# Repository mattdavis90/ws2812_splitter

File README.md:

# WS2812 Splitter

> [!WARNING]
> This project is still very much in beta and I am yet to receive the PCBs and fully verify the desgn.

A configurable splitter compatible with WS2812(B) LEDs. Splits the incoming signal two ways; the first is a copy of the input and the second is disabled for N LED's worth of data. This allows you to run two strips in parallel with each other.

The project is based on the work by [Pete on hackaday.io](https://hackaday.io/project/8181-ws2812b-delay-splitter). As far as I can tell Pete never got it working, this is intended to be a continuation of that work.

The project is being used personally for WS2812B Icicles. Rather than running wires from the bottom of each icicle back to the next LED (to create a continuous strip) this project allows you to place a 'tee' at the top of each icicle, that delays the continuing signal by the length of the drop.

This is maybe best viewed as an image

## Hardware

The design uses a Renesas SLG46826 SPLD to implement the logic required to detect the reset period, count LED words and generate the split signal.

A custom PCB was designed using the TSSOP-20 package to ease soldering. On board are 4 solder jumpers that set the length of the drop; between 0 and 15 LEDs.

### Renesas Greenpak Designer

The Renesas Greenpak software is free to download. I used the Ubuntu version successfully on Fedora. Mac and Windows are also available. This is a screenshot of the design I came up with. I went the multi-programmable chips; a little bit more expensive but I wanted to be sure the design worked and could be tweaked.

*Note*: Counters reset to `N` and trigger on 0 so should be set to `N-1`

Break down of macrocells

* Reset Detector
    - WS2812 datasheet states a minimum 50us reset period - data line held low
    - CNT0 is clocked by OSC2 at 25MHz, counting to 1249 (50us)
    - Generates `rst` and `nRst` nets
* Bit Counter
    - Clocked by incoming data on rising edges
    - Reset by the `rst` net
    - Counter set to 23 (24b - 1) generating a per-LED pulse
* Word Counter
    - Uses the built-in 3-bit ripple counter
    - Additionally a DFF is used to add a 4th bit to the counter
    - The counter is reset by `nRst`
* Delay Comparator
    - Compares the output of the ripple counter with the user input
    - The comparisons are ANDed together to generate an *output enable* signal
    - To fix the timing the Word Counter pulse is removed from the *output enable* signal
* Hold
    - The LUT acts as an SR-FlipFlop to hold the output latch High after the first comparison
    - The latch is reset by the `rst` net after >=50us of now input data

The design leaves several blocks unused which could be used to expand to >15 LEDs in future.

### PCB

The PCB is designed using KiCad 7 and manufactured by JLCPCB.

I aimed to keep in compact while still allowing hand soldering. The design uses the TSSOP package for the SLG and 0805 (2012) resistors and capacitors. The input signal is on `J2`, `J3` carries a regenerated signal down the icicle, `J4` carries the signal that is missing the first `N` LEDs worth of data; LEDs after this point will act as though they are at the end of the icicle.

`N` is set using `JP1-4` using binary - the pads can be soldered and desoldered easily.

## Programming

The `J1` header on the PCB is designed as a programming header. It provides power and I2C connectivity to the chip. To program the SLG46826 I used a pogo pin assembly from eBay and a CH341A chip. I'm using [this](https://github.com/Steve-Tech/i2c-ch341-usb) fork of the Linux CH341A I2C module because it supports kernel 6.4+

I wrote a custom SLG programmer to talk I2C over a standard Linux `/dev/i2c-#` device, available [here](https://github.com/mattdavis90/slg_programmer)

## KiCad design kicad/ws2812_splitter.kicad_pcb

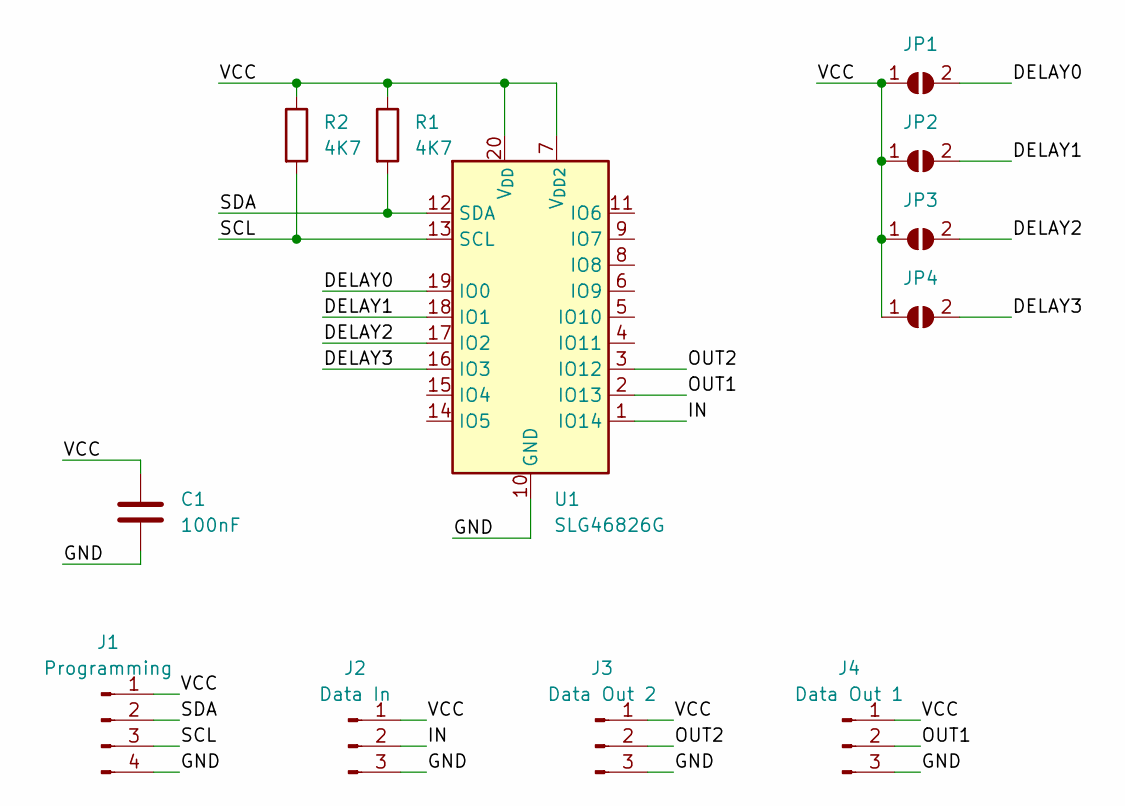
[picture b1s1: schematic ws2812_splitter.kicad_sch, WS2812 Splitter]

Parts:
C1: 100nF; C_0805_2012Metric_Pad1.18x1.45mm_HandSolder
J1: Programming; PinSocket_1x04_P2.54mm_Vertical
J2: Data In; PinSocket_1x03_P2.54mm_Vertical
J3: Data Out 2; PinSocket_1x03_P2.54mm_Vertical
J4: Data Out 1; PinSocket_1x03_P2.54mm_Vertical
JP1: Delay0; SolderJumper-2_P1.3mm_Open_Pad1.0x1.5mm
JP2: Delay1; SolderJumper-2_P1.3mm_Open_Pad1.0x1.5mm
JP3: Delay2; SolderJumper-2_P1.3mm_Open_Pad1.0x1.5mm
JP4: Delay3; SolderJumper-2_P1.3mm_Open_Pad1.0x1.5mm
R1, R2: 4K7; R_0805_2012Metric_Pad1.20x1.40mm_HandSolder
U1: SLG46826G; TSSOP-20_4.4x6.5mm_P0.65mm

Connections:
/DELAY0: JP1.2 (B), U1.19 (IO0)
/DELAY1: JP2.2 (B), U1.18 (IO1)
/DELAY2: JP3.2 (B), U1.17 (IO2)
/DELAY3: JP4.2 (B), U1.16 (IO3)
/GND: C1.2, J1.4, J2.3, J3.3, J4.3, U1.10 (GND)
/IN: J2.2, U1.1 (IO14)
/OUT1: J4.2, U1.2 (IO13)
/OUT2: J3.2, U1.3 (IO12)
/SCL: J1.3, R2.2, U1.13 (SCL)
/SDA: J1.2, R1.2, U1.12 (SDA)
/VCC: C1.1, J1.1, J2.1, J3.1, J4.1, JP1.1 (A), JP2.1 (A), JP3.1 (A), JP4.1 (A), R1.1, R2.1, U1.7 (V_{DD2}), U1.20 (V_{DD})

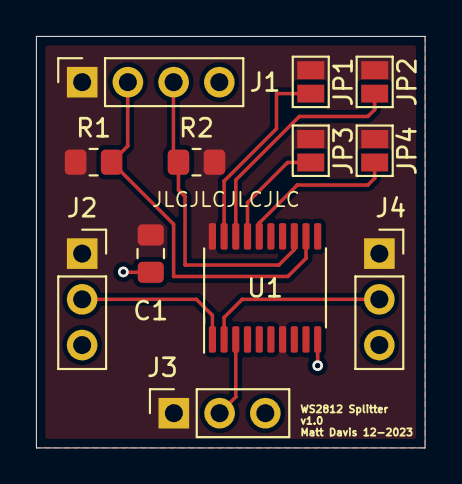
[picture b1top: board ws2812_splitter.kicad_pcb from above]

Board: 2 copper layers, 21.6 x 22.9 mm, 12 parts (0 on the bottom side), 11 nets.

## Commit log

2023-12-31 chore: shrink images and add warning
